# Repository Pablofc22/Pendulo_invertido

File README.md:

# Pendulo_invertido

En este repositorio se encuentra los sigientes apartados sobre el proyecto del péndulo invertido.

* Diseño de chasis en la plataformade FreeCad
* Diseño de PCB en KiCad
* Foto final del péndulo

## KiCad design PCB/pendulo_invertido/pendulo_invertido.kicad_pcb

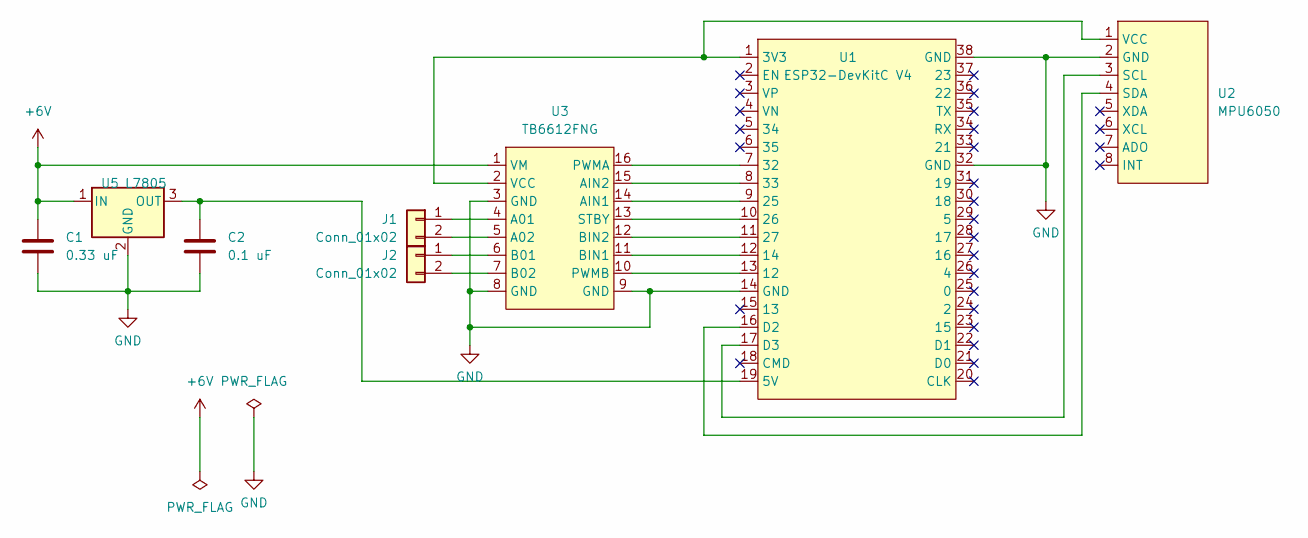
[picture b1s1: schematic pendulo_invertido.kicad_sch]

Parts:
C1: 0.33 uF; C_Radial_D5.0mm_H11.0mm_P2.00mm
C2: 0.1 uF; C_Radial_D5.0mm_H11.0mm_P2.00mm
J1, J2: Conn_01x02; JST_XH_B2B-XH-A_1x02_P2.50mm_Vertical
U1: ESP32-DevKitC V4; ESP32-DevKitC
U2: MPU6050
U3: TB6612FNG
U5: L7805; TO-220-3_Vertical

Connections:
+6V: C1.1, U3.1 (VM), U5.1 (IN); also elsewhere on the board
GND: C1.2, C2.2, U1.14 (GND), U1.32 (GND), U1.38 (GND), U2.2 (GND), U3.3 (GND), U3.8 (GND), U3.9 (GND), U5.2 (GND); also elsewhere on the board
unnamed: J1.1, U3.4 (A01)
unnamed: J1.2, U3.5 (A02)
unnamed: J2.1, U3.6 (B01)
unnamed: J2.2, U3.7 (B02)
unnamed: U1.1 (3V3), U2.1 (VCC), U3.2 (VCC)
unnamed: C2.1, U1.19 (5V), U5.3 (OUT)
unnamed: U1.13 (12), U3.10 (PWMB)
unnamed: U1.12 (14), U3.11 (BIN1)
unnamed: U1.9 (25), U3.14 (AIN1)
unnamed: U1.10 (26), U3.13 (STBY)
unnamed: U1.11 (27), U3.12 (BIN2)
unnamed: U1.7 (32), U3.16 (PWMA)
unnamed: U1.8 (33), U3.15 (AIN2)
unnamed: U1.16 (D2), U2.4 (SDA)
unnamed: U1.17 (D3), U2.3 (SCL)

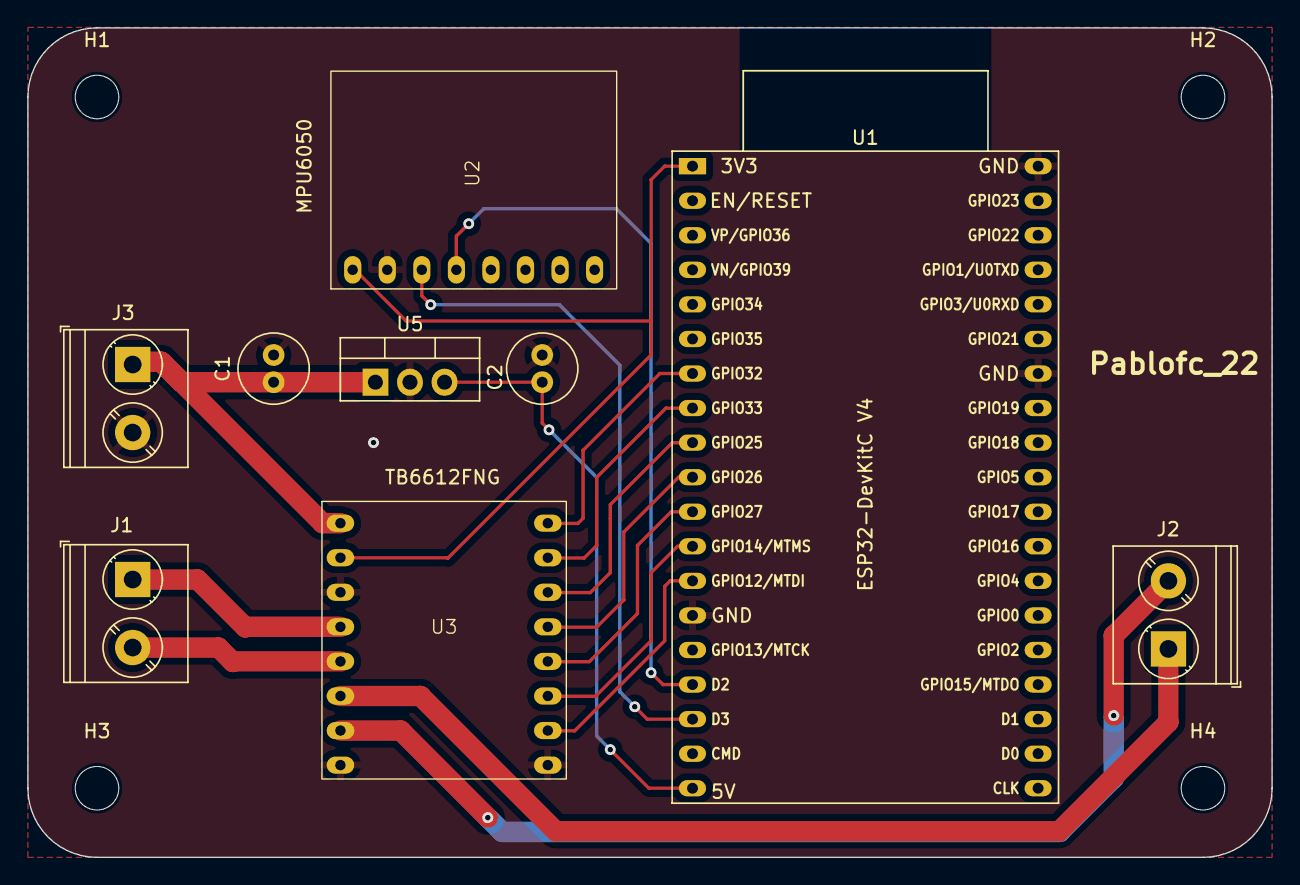
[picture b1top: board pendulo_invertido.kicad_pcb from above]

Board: 2 copper layers, 91.4 x 61.0 mm, 13 parts (0 on the bottom side), 17 nets.

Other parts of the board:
H1, H2, H3, H4: MountingHole_3.2mm_M3
J3: TerminalBlock_Phoenix_PT-1,5-2-5.0-H_1x02_P5.00mm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; TerminalBlock_Phoenix_PT-1,5-2-5.0-H_1x02_P5.00mm_Horizontal

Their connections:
+6V: J3.1; also elsewhere on the board
GND: J3.2; also elsewhere on the board

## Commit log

2024-03-27 Cambios en el esquematico
2024-04-02 prototipo diseño PCB
2024-04-04 modificaciones prototipo
2024-04-18 PCB finalizada y pedida
2024-04-20 Comienzo de chasis
2024-05-01 Chasis finalizado e impreso
2025-06-03 Foto péndulo final
2025-06-03 cambios en el README.md
